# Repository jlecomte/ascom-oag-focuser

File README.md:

# ASCOM-Compatible OAG Focuser

I do not charge anything to create and maintain these open-source projects. But if you would like to say "thanks" for this project, feel free to send any amount through Paypal using the button below. I appreciate your support!

<!-- toc -->

- [Introduction](#introduction)
  * [Is This For You?](#is-this-for-you)
  * [Use As A Standalone Focuser](#use-as-a-standalone-focuser)
- [Finished Product](#finished-product)
- [Demo](#demo)
- [Pre-Requisites](#pre-requisites)
- [Hardware / BOM](#hardware--bom)
- [ASCOM Driver](#ascom-driver)
  * [Downloading And Installing The Driver](#downloading-and-installing-the-driver)
  * [Compiling The Driver (For Developers Only)](#compiling-the-driver-for-developers-only)
  * [Screenshots](#screenshots)
- [Standalone Focuser Application](#standalone-focuser-application)
- [Arduino Firmware](#arduino-firmware)
  * [Microcontroller Compatibility](#microcontroller-compatibility)
  * [Compiling And Uploading The Firmware](#compiling-and-uploading-the-firmware)
- [Electronic Circuit](#electronic-circuit)
- [Mechanical Components](#mechanical-components)
  * [OAG Compatibility](#oag-compatibility)
  * [Gear And Pinion](#gear-and-pinion)
- [Calibration Procedure](#calibration-procedure)
- [Troubleshooting](#troubleshooting)
- [Frequently Asked Questions (FAQ)](#frequently-asked-questions-faq)
- [Credits](#credits)

<!-- tocstop -->

## Introduction

Shortly after I got started in astrophotography, I noticed that the stars in my images were slightly elongated due to some differential flexure somewhere in my imaging system (see [Cloudy Nights thread](https://www.cloudynights.com/topic/775260-good-guiding-but-elongated-stars-along-e-w-direction/) — I strongly suspect that it is sag in my focuser...) The permanent solution was to switch from using a guide scope to using an off-axis guider (OAG) and that immediately resolved my issue. Now, my stars are perfectly round, which is great! For reference, I purchased the [ZWO OAG](https://astronomy-imaging-camera.com/product/zwo-oag) and the accompanying [ZWO 1.25" helical focuser](https://astronomy-imaging-camera.com/product/zwo-1-25%E2%80%B3-helical-focuser).

As good as this sounds, the OAG brought a number of new challenges which I did not have to deal with before. First, when using an OAG, the field of view is very small, which sometimes makes it difficult for the guiding software to detect guide stars. Second, the OAG requires some amount of refocusing when switching filters. Indeed, filters are not always parfocal. Most importantly, a refractor (even an apochromatic triplet...) will focus various wavelengths at different distances, and this is the primary reason why it is required to change the focus of the main imaging camera (using filter offsets) when changing filters. Unfortunately, while the imaging sensor is located _behind_ the filter wheel, the OAG is always placed _before_ the filter wheel (Otherwise, especially when using narrowband filters, you would not be able to find a single guide star... Also, placing the filter wheel further away from the imaging sensor would cause vignetting...) and this is why, under specific conditions (see "Is this For You" paragraph below), the guide camera might show out-of-focus images while the imaging camera is in focus, and even though the guide camera was independently focused while another filter was selected in the filter wheel.

While guiding software like PHD2 can accommodate slightly out-of-focus guide stars by computing their centroid, out-of-focus guide images can contain a drastically lower number of detected guide stars, and those that are detected will have a much lower Signal to Noise Ratio (SNR), further reducing the accuracy of the centroid computation. In some situations, PHD2 may not even be able to detect a single guide star, and guiding will be impossible. This has happened to me in the past, and I was forced to _manually_ refocus the guide camera (independently of the main imaging camera of course, using the OAG helical focuser)

Manually refocusing the guide camera throughout the night is not exactly one of the most enjoyable parts of the hobby, so I looked for ways to automate that. Pegasus Astro sells a motorized OAG named [SCOPS OAG](https://pegasusastro.com/products/scops-oag/). However, it is a little expensive for me ($750 US — although it is a really great looking unit!) Furthermore, I discussed with the [N.I.N.A.](https://nighttime-imaging.eu/) developers on their [Discord server](https://discord.gg/fwpmHU4). Since N.I.N.A. can only connect to a single focuser at a time, there is no good solution yet to deal with SCOPS OAG. It is certainly possible to run a second instance of N.I.N.A. that connects to both SCOPS OAG and the guide camera, but there is no way to have those two N.I.N.A. instances communicate to do something upon filter change.

All of this has led me to design and build my own solution to this problem. In this repository, you will find everything you need to motorize and automatically control the ZWO OAG (list of parts, 3D model, electronic schematics, Arduino firmware, ASCOM driver, standalone ASCOM client application, instructions, etc.) I hope you consider building this project if you find yourself in a similar situation. Please note that the ASCOM driver can be used with SCOPS OAG, there is nothing in the Filter Wheel Proxy implementation that is specific to my device.

### Is This For You?

Not necessarily! It really depends on a lot of factors. For example, if you are using a mirrored telescope, i.e. not a refractor, and if all of your filters come from the same set, e.g., Antlia LRGB filter set, and the filter manufacturer claims they are parfocal, then you may not need this at all because the difference in focus between filters will be so minuscule, you probably won't need to worry about it. However, if you are using a refractor (even an APO triplet), or if you use filters that are not parfocal, you _may_ need this. The only way to find out is to focus your main imaging camera, and then, assuming that you've already defined your filter offsets, go through every single filter in your filter wheel. After every filter change, your imaging application will adjust the focus of your imaging train slightly depending on the filter offset you have defined for the selected filter, and you should look at the image coming out of your guide camera in PHD2. In my case, the stars in my guide camera can be pinpoint when I am using my Luminance filter, but they are large disks when I am on some other filter. That is how you know that this device can be useful for you. This definitely is not for everybody, but the people who have the problem I just described did not really have a good solution until now.

### Use As A Standalone Focuser

Please note that you can use this device, and the accompanying software, to motorize any helical focuser, regardless of how you use that focuser. For example, you could use it to control the focus of a guide scope or even an entire imaging train! Some people have used this project to motorize the focus of a spectrograph. Just remember that if you have a helical focuser that is not from ZWO, you may need to make a few adjustments to the 3D model...

## Finished Product

Here is what the finished product looks like:

And here it is, attached to the ZWO OAG, and fitted with a guide camera:

## Demo

Here is a demo of the system when attached to my telescope, and used as an OAG focuser:

The following video shows what the guide camera sees with and without the OAG focuser upon switching to a different filter:

## Pre-Requisites

* A Windows computer (Windows 10 or newer)
* [Microsoft Visual Studio](https://visualstudio.microsoft.com/) (FYI, I used the 2022 edition...)
* [ASCOM Platform](https://ascom-standards.org/)
* [ASCOM Platform Developer Components](https://ascom-standards.org/COMDeveloper/Index.htm)
* [Arduino IDE](https://www.arduino.cc/en/software)
* [FreeCAD](https://www.freecadweb.org/), a free and open-source 3D parametric modeler
* A 3D printer able to print PETG, and a slicer (I use a heavily upgraded Creality Ender 3 v2, and Ultimaker Cura)
* A few basic tools that any tinkerer must own, such as a breadboard, a soldering iron, etc.

## Hardware / BOM

* [ZWO 1.25" helical focuser](https://bit.ly/47JOTRL) or equivalent.
* Arduino-compatible microcontroller board with built-in EEPROM support. I used an [Arduino Nano clone with a USB-C connector (~$10 USD on Amazon for a pack of 3...)](https://www.amazon.com/dp/B09DKHWSY9?tag=darkskygeek-20)
* [ULN2003 Darlington transistor array](https://www.amazon.com/dp/B0CBM23ZJ3?tag=darkskygeek-20) to control the stepper motor using the Arduino's digital I/O pins.
* [28BYJ-48 stepper motor (5V)](https://www.amazon.com/dp/B01CP18J4A?tag=darkskygeek-20)
* [LEDs](https://www.amazon.com/dp/B09XDMJ6KY?tag=darkskygeek-20) and [resistors](https://www.amazon.com/dp/B08FD1XVL6?tag=darkskygeek-20) — These are not required, but they can be useful to debug the firmware while prototyping.
* Connectors — I used [JST-XH connectors](https://www.amazon.com/dp/B01MCZE2HM?tag=darkskygeek-20), only because I already had a bunch of them, along with [a crimping tool](https://www.amazon.com/dp/B078WNZ9FW?tag=darkskygeek-20).
* [Capacitors](https://www.amazon.com/dp/B07PBQXQNQ?tag=darkskygeek-20) — Any 10 to 20µF cpacitor should work (this is just a bulk capacitor, so the exact value does not matter)
* [M2 Threaded Inserts](https://www.amazon.com/dp/B0B8GN63S2?tag=darkskygeek-20)
* [M3 Threaded Inserts](https://www.amazon.com/dp/B0BQJ6CRNJ?tag=darkskygeek-20)

## ASCOM Driver

### Downloading And Installing The Driver

Starting with version `1.0.5`, you can install the ASCOM driver, as well as the standalone focuser control application, by running the executable setup file that you will find in the [releases page](https://github.com/jlecomte/ascom-oag-focuser/releases). By default, it places files under `C:\Program Files (x86)\Dark Sky Geek\OAG Focuser ASCOM Driver`.

### Compiling The Driver (For Developers Only)

Open Microsoft Visual Studio as an administrator (right-click on the Microsoft Visual Studio shortcut, and select "Run as administrator"). This is required because when building the code, by default, Microsoft Visual Studio will register the compiled COM components, and this operation requires special privileges (Note: This is something you can disable in the project settings...) Then, open the solution (`ASCOM_Driver\ASCOM.DarkSkyGeek.OAGFocuser.sln`), change the solution configuration to `Release` (in the toolbar), open the `Build` menu, and click on `Build Solution`. As long as you have properly installed all the required dependencies, the build should succeed and the ASCOM driver will be registered on your system. The binary file generated will be `ASCOM_Driver\bin\Release\ASCOM.DarkSkyGeek.OAGFocuser.dll`. You may also download this file from the [Releases page](https://github.com/jlecomte/ascom-oag-focuser/releases).

### Screenshots

The ASCOM driver registers two new components: `ASCOM.DarkSkyGeek.FilterWheelProxy`, which implements the `IFilterWheelV2` ASCOM interface, and `ASCOM.DarkSkyGeek.OAGFocuser`, which implements the `IFocuserV3` ASCOM interface. Both components have their own settings dialog. Here is what the filter wheel settings dialog looks like:

And here is what the focuser settings dialog looks like:

## Standalone Focuser Application

Open the `Focuser_App\ASCOM.DarkSkyGeek.FocuserApp.sln` solution in Microsoft Visual Studio, change the solution configuration to `Release` (in the toolbar), open the `Build` menu, and click on `Build Solution`. Very simple! The binary file generated will be `Focuser_App\bin\Release\ASCOM.DarkSkyGeek.FocuserApp.exe`. You may also download this file from the [Releases page](https://github.com/jlecomte/ascom-oag-focuser/releases). Here is what that little standalone application looks like:

This application allows you to connect to and control DarkSkyGeek’s OAG focuser, and in particular, it enables you to test various backlash compensation values as well as set the zero position. If you use a SCOPS OAG, I can only assume that it came with its own standalone application with similar functionality...

## Arduino Firmware

### Microcontroller Compatibility

All Arduino-compatible microcontrollers that have a **built-in EEPROM** should work. Unfortunately, this excludes the popular [Seeeduino XIAO](https://www.seeedstudio.com/Seeeduino-XIAO-Arduino-Microcontroller-SAMD21-Cortex-M0+-p-4426.html) (one of my favorite microcontroller boards for hobby projects...) If you insist on using a unit that does not have a built-in EEPROM, you will have to customize the firmware to fit your needs. You could technically use a separate EEPROM chip, or you could use the [`FlashStorage` library](https://github.com/cmaglie/FlashStorage) or the [`FlashStorage_SAMD` library](https://github.com/khoih-prog/FlashStorage_SAMD), or you could simply disable the EEPROM code (in which case the device will not remember its last position after a power cycle...) There are quite a few options to choose from, but I recommend using something like an Arduino Nano for example, which is small, affordable, and has everything you need.

**Note:** I tried several Arduino nano clones, and they do not all work. Some of them seem to work, but not reliably. I did not investigate too deeply, but I think it is because their BOD (Brown Out Detection) levels are set too low. When the motor turns, the voltage used to power the microcontroller will drop slightly, and if it drop below a certain level, some units will simply reset themselves in an act of self-protection. So, I strongly recommend the unit linked above, in the BOM list.

### Compiling And Uploading The Firmware

* If needed, add support for the board that you are using in your project.
* You may want to customize the name of the device when connected to your computer. To do that, you will have to update the appropriate `usb_product` key in the appropriate `boards.txt` file... I cannot give you specific instructions for that because they depend on the exact board you are using.
* Finally, connect your board to your computer using a USB cable, open the sketch file located at `Arduino_Firmware\Arduino_Firmware.ino`, and click on the `Upload` button in the toolbar.

## Electronic Circuit

The electronics circuit is fairly straightforward. I included a Fritzing file in the `Electronics/` folder. Here are the schematics:

Here is what the prototype circuit looks like:

Here is what the PCB looks like when rendered in KiCad:

Here is what the real PCB looks like:

## Mechanical Components

### OAG Compatibility

In case you are planning to use this electronic focuser with an OAG, please note that [the standard version](3D_Files/Standard-Version/) is compatible (out of the box) with the following OAGs:

* ✅ **ZWO OAG** (standard version)
* ✅ **ZWO OAG-L** (large version) via [this adapter](3D_Files/ZWO-OAG-L/Adapter.FCStd).
* ✅ **Askar OAG**
* ✅ **Player One OAG** (MIN or MAX)

Additionally, an OpenSCAD model designed for the **Celestron OAG** was generously provided by [Endymion42](https://github.com/Endymion42). For more information and photographs, please refer to [this GitHub issue](https://github.com/jlecomte/ascom-oag-focuser/issues/10). The files can be found [here](3D_Files/Celestron-OAG/). **Important note: I will not provide any support whatsoever for this version, so use at your own risk!**

And finally, please note that this electronic focuser is NOT compatible with the following OAGs (at least not without a significant design change):

* 🛑 **QHY OAG**
* 🛑 **Touptek OAG**
* 🛑 **OGMA OAG** — The helical focuser cannot be removed, so you would have to slightly tweak the design of this project to make it fit.
* 🛑 **Antlia OAG** — The helical focuser can be detached from that unit, exposing an M42 male thread, so you would think it might work. However, due to the square OAG body, the stepper motor gets in the way. In my design, the stepper motor sticks out under the body of the electronic focuser to minimize the space the entire unit takes when used with a round OAG. **Note:** Some people have successfully adapted my design to flip the motor around and make it work with this unit.

### Gear And Pinion

In [the first version of this project](https://github.com/jlecomte/ascom-oag-focuser/tree/v1), I was using helical gears. However, this was not a very smart choice because the axial force that results from this design, and the fact that the stepper motor shaft has a bit of longitudinal play caused the backlash to be a bit higher than I would have liked. While it still worked well (thanks to backlash compensation), this new version uses a herringbone pattern for the gear and pinion:

It turns out that gears are easy to make on a 3D printer, and work flawlessly. However, here are a few tips I found useful:

* Dry your filament to reduce problems, specifically stringing to a minimum
* Use the proper Z offset, and (if needed) set the initial layer horizontal expansion value in Cura to a negative number, e.g., -0.2mm. It is critical to prevent the dreaded "elephant's foot" (squishing of the first layer)
* To ensure that the first layer adheres well, clean your build plate (I use denatured alcohol)

Another trick that also helped get great results was to slightly loosen the focuser (there are 4 tiny set screws on the ZWO focuser that you can loosen _ever so slightly_ to make it easier to rotate the knurled knob) because these small stepper motors don't have that much torque...

The focuser gear slips onto the knurled knob of the helical focuser. The pinion slips onto the motor shaft, although it might require a light hammer blow to get it fully seated. It is not necessary to use any glue to keep the gears in place.

## Calibration Procedure

Before you can use this device, you have to calibrate it. Here is the procedure:

1. **Filter Offsets Measurement**

   Measuring filter offsets is something you have probably already done because it allows you to run an autofocus routine using your luminance (L) filter, which can be done with very short exposures, thereby saving a lot of time (it is also more accurate). Enter the filter offsets in your imaging application, e.g., N.I.N.A., as well as in the settings dialog of the `DarkSkyGeek’s Filter Wheel Proxy For OAG Focuser` ASCOM device (see screenshot above). Remember that it is critical that your imaging application and the driver have the same filter offset values!

   **Note:** If you measure your filter offsets with a reducer, they will be different. Don't worry about that. Do the entire calibration procedure with your standard astrophotography setup. Once properly set up, the OAG focuser configuration will not need to change whether or not you add a reducer to your imaging train.

2. **Backlash Measurement**

   There are many sources of backlash in this system. The stepper motor itself, due to its internal gearbox, already has some amount of backlash. The 3D printed gear and pinion also have some backlash. And finally, the helical focuser has some backlash as well. All of those sources combine. Thankfully, compensating for backlash is easy and supported by the software in this repository. The trick is to first measure the amount of backlash in your system. That is done using a dial gauge. Please refer to the video below for more details.

   Using the standalone focuser control application, setting a backlash compensation of 0, move in one direction by a large amount. Then, repetitively move in small increments in the opposite direction until the dial indicator starts moving. In my setup, I have a total of about 60 steps of backlash, so I set the backlash compensation amount to 150 (the software uses the so-called "overshoot" backlash compensation method) and it works absolutely flawlessly! Enter the value of the backlash, in number of steps (150 in my case), in the settings dialog of the `DarkSkyGeek’s Filter Wheel Proxy For OAG Focuser` ASCOM device (see screenshot above)

3. **Zero Position**

   Manually rotate the OAG focuser until it hits its mechanical zero position. Connect the OAG focuser to a computer (assuming you had previously installed the OAG focuser ASCOM driver on that computer), open the standalone focuser app, connect to the device, and click on the "Set Zero position!" button.

4. **Steps Ratio Measurement**

   The "steps ratio" allows the Filter Wheel Proxy ASCOM driver to answer the following question: Upon filter change, the main focuser has to move n steps in this direction. How many steps does the OAG focuser need to move, and in which direction?

   The best way to measure the steps ratio is to use 2 instances of N.I.N.A. The first instance is connected to the telescope focuser and the main imaging camera. The second instance is connected to the OAG focuser and the guide camera. Then, follow these steps:

   * Run an autofocus routine in both N.I.N.A. instances (start with the one that controls the telescope focuser and the main imaging camera)
   * Take note of the position of the OAG focuser.
   * Move the telescope focuser by, for example, 300 steps outward.
   * Run another autofocus routine on the second N.I.N.A. instance (the one that controls the OAG focuser and the guide camera)
   * Subtract the new position of the OAG focuser with the initial position, and divide that number by the number of steps you moved the main telescope focuser (300 in our example). That will give you the steps ratio. Note that this will be a negative number. In my case, the steps ratio is -2.64.
   * You can run the autofocus routine several times, and average the positions obtained to increase accuracy.
   * Enter the steps ratio in the settings dialog of the `DarkSkyGeek’s Filter Wheel Proxy For OAG Focuser` ASCOM device (see screenshot above)

5. **Test**

   Once you have calibrated the OAG Focuser, you can close the second instance of N.I.N.A. and open PHD2. Use the first instance of N.I.N.A. as you normally would, although instead of connecting your filter wheel directly, you will connect to the `DarkSkyGeek’s Filter Wheel Proxy For OAG Focuser` device. Looking at the PHD2 live view, change the filter in the filter wheel and watch the PHD2 live view becoming blurry and then sharp again, automatically! Isn't technology beautiful?!

This procedure is explained in great detail in the following video:

## Troubleshooting

**The standalone focuser application is not able to connect to the device**

**Step 1:** On Windows, open the Device Manager, and expand the `Ports (COM & LPT)` section. Connect the Arduino. You should see a new COM port appear. If you don't, there is a problem with Windows, the Arduino, or the USB cable.

**Step 2:** Assuming that a new COM port appeared in step 1, open the driver settings dialog from the standalone focuser application, and ensure that you have the `Auto-Detect COM port` option enabled.

**Step 3:** Make sure that no other application is currently using the COM port assigned to the device. On Windows, a single process can be connected to a COM port at any given time, so if you happen to be running the Arduino IDE (for example) at the same time, it will have likely automatically connected to the Arduino via the COM port, and the standalone focuser application will not be able to connect.

**Step 4:** If all else fails, look for the driver logs under `<DOCUMENTS FOLDER>\ASCOM\Logs <DATE>\` and open the most recent file. Feel free to open an issue, and paste the content of the log file.

**The focuser turns in the wrong direction**

Depending on how you wire the stepper motor, it may turn in different directions. This is especially important when you first try the device, because its position is set to 0 by default and the driver will throw an error if the position becomes negative. So if you encounter an error on first try, don't worry! Disconnect the focuser in the application (no need to disconnect the USB cable...), open the focuser settings dialog, toggle the "Reverse Rotation" option (see screenshot above), and click OK. Then, connect to the focuser and try again.

## Frequently Asked Questions (FAQ)

**I built this project and it does not work, can you help?**

_Maybe. As indicated in the `LICENSE` file, I do not provide any official guarantee or support. That being said, if you open a GitHub issue in this repository and ask nicely, I will likely respond. Just make sure that you provide all the necessary details so that I understand what the issue might be. While on that note, keep in mind that troubleshooting an issue on your own is by far the best way to learn new things._

**Why did you not use the `Stepper` or `AccelStepper` library in the Arduino firmware?**

_It might seem strange that I decided to "manually" control the stepper motor instead of using the standard [`Stepper` library](https://www.arduino.cc/reference/en/libraries/stepper/) or the popular [`AccelStepper` library](https://www.arduino.cc/reference/en/libraries/accelstepper/). There are two reasons for that:_

1. _I need to be able to handle incoming requests while the motor is moving, e.g., `COMMAND:FOCUSER:ISMOVING` or `COMMAND:FOCUSER:HALT`. This is not possible with any of the aforementioned libraries._
2. _To save power, to prevent heat buildup, and to eliminate vibrations, I de-energize the stepper motor by setting all the pins to LOW once it has reached the desired position. This is also not supported by any of the aforementioned libraries, and it makes a huge difference! If you don't believe me, try commenting out that part of the code, and play with the firmware for a little while (you don't even need to actively move the motor). Then, feel how hot the motor gets... Also, feel how much the motor vibrates while energized, and consider the impact that might have on your images..._

**Why is backlash compensation not implemented in the focuser driver?**

_The software included in this repository (specifically the `FilterWheelProxy` ASCOM component) was designed and implemented so that it may be used with other OAG focusers, including commercial units such as the SCOPS OAG, and I have no idea whether their driver handles backlash compensation. This way, no matter which focuser you use to adjust the focus of your guide camera, as long as its driver implements the standard `IFocuserV3` ASCOM interface, this will work and you will enjoy the benefits of backlash compensation!_

**What is the positional accuracy of this focuser?**

_Using a precision dial indicator (see "Backlash Measurement" section), I was able to measure the positional accuracy of this device (move 1,000 steps in one direction, move 1,000 steps in the opposite direction, and measure the difference between the starting and ending positions). Astoundingly, it is of the order of about 10μm!_

**My antivirus identifies your setup executable file as a malware (some kind of Trojan)**

_This is a false detection, extremely common with installers created with [Inno Setup](https://jrsoftware.org/isinfo.php) because virus and malware authors also use Inno Setup to distribute their malicious payload... Anyway, there isn't much I can do about this, short of signing the executable. Unfortunately, that would require a code signing certificate, which costs money. So, even though the executable I uploaded to GitHub is perfectly safe, use at your own risk!_

## Credits

I would like to thank _Christophe de la Chapelle_ of the popular French-language YouTube channel [La Chaîne Astro](https://www.youtube.com/c/cdlc48) because he gave me the idea to build a focuser for my OAG after he demonstrated how he had built a simple focuser using 3D printed parts and a stepper motor for his telescope.

I would like to also thank _Stefan Berg_, creator of [N.I.N.A.](https://nighttime-imaging.eu/), and _Linwood Ferguson_ (see [his web site](https://www.captivephotons.com/Photography/Astrophotography/)) for giving me the idea to create a "proxy" filter wheel component while discussing the design of this system on the [N.I.N.A. Discord server](https://discord.gg/fwpmHU4).

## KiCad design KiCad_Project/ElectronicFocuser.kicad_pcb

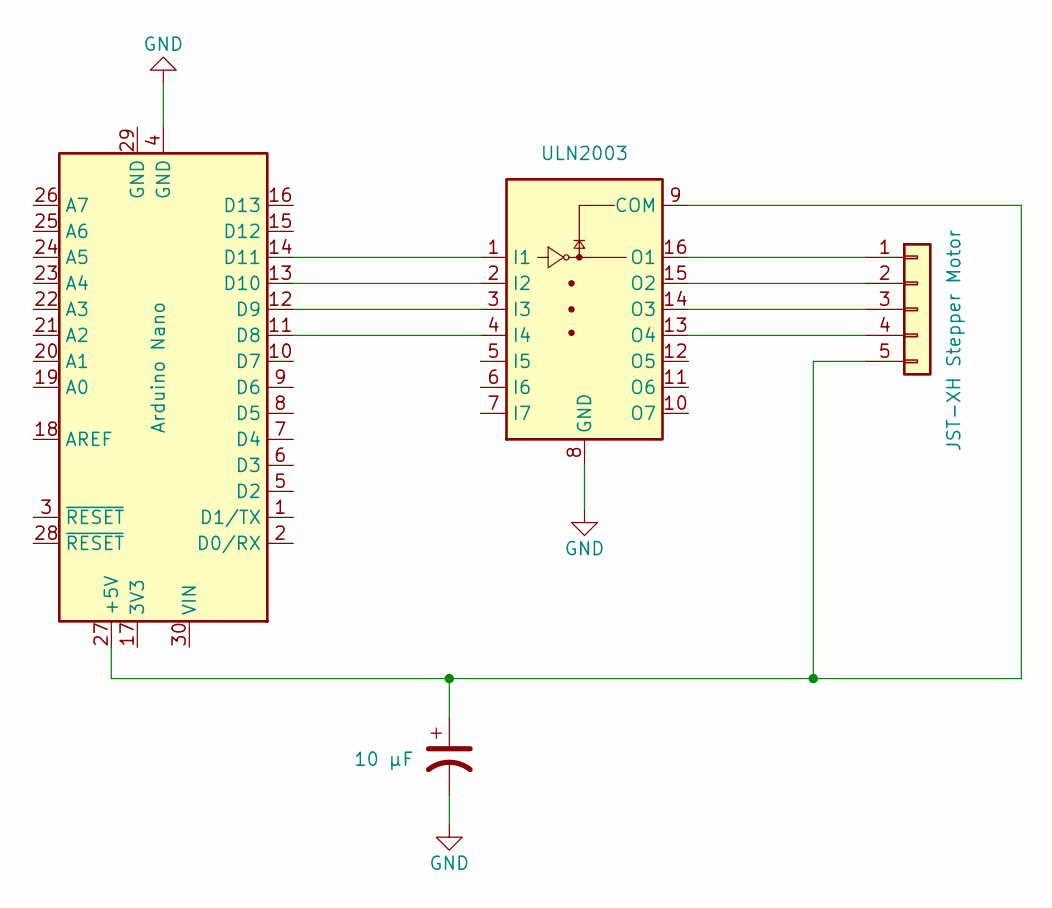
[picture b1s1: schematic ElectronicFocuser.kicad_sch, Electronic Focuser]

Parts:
A1: Arduino Nano; Arduino_Nano
C1: 10 µF; CP_Radial_D4.0mm_P2.00mm
J1: JST-XH Stepper Motor; JST_XH_B5B-XH-A_1x05_P2.50mm_Vertical
U1: ULN2003; DIP-16_W7.62mm

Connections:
GND: A1.4 (GND), C1.2, U1.8 (GND)
unnamed: A1.11 (D8), U1.4 (I4)
unnamed: A1.12 (D9), U1.3 (I3)
unnamed: A1.13 (D10), U1.2 (I2)
unnamed: A1.14 (D11), U1.1 (I1)
unnamed: A1.27 (+5V), C1.1, J1.5, U1.9 (COM)
unnamed: J1.1, U1.16 (O1)
unnamed: J1.2, U1.15 (O2)
unnamed: J1.3, U1.14 (O3)
unnamed: J1.4, U1.13 (O4)

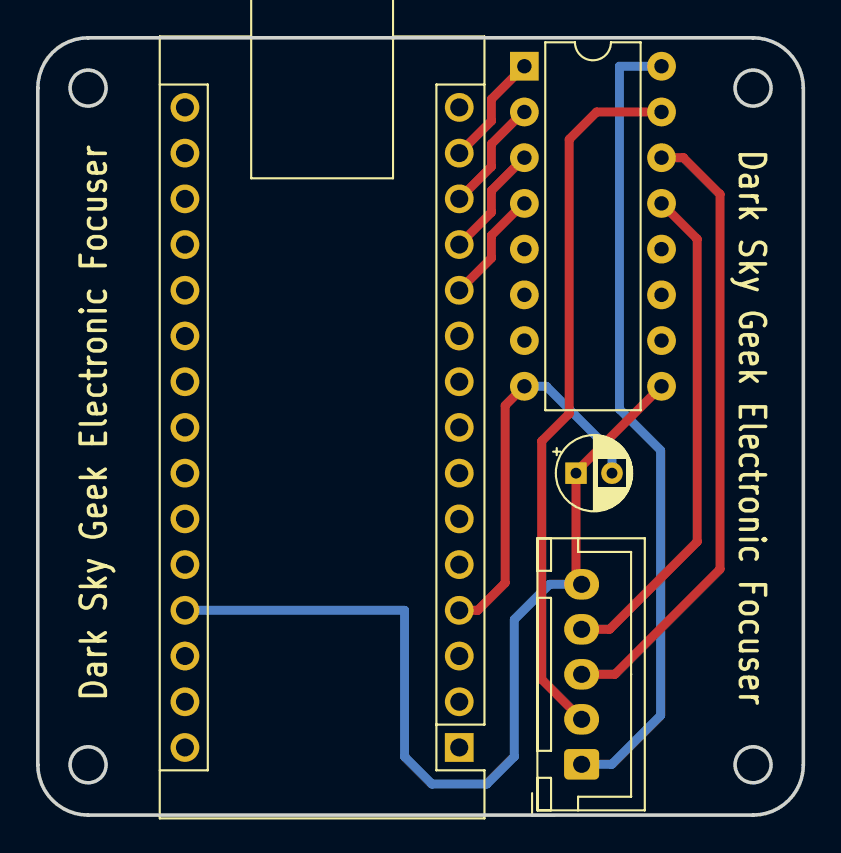
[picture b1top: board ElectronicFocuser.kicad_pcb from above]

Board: 2 copper layers, 42.5 x 43.2 mm, 4 parts (0 on the bottom side), 10 nets.

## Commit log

2022-05-22 Updated project file
2022-05-22 Fixed initial set of bugs
2022-05-23 First working working!
2022-05-23 Fix heat build up by powering off the stepper when idle
2022-05-23 Updated comment
2022-05-23 Code cleanup + added backlash handling and leveraged step ratio
2022-05-24 Added first 3D files
2022-05-24 Added images
2022-05-25 Added standalone focuser app
2022-05-25 Fixed lots and lots of small - and not so small - issues
2022-05-25 Small tweaks to make the driver work with scops OAG
2022-05-25 Few minor fixes to focuser app
2022-05-25 Added electronics schematics
2022-05-25 Updated images
2022-05-25 Renamed standalone focuser app binary
2022-05-25 Updated README and images
2022-05-25 Added copyright header that was missing in a few files
2022-05-26 Fixed small routing issue in electronics schematics
2022-05-28 Allow focuser to reverse rotation due to gearing
2022-06-06 Added all necessary 3D files
2022-06-16 Added calibration procedure
2022-06-25 Fixed minor bugs found during testing
2022-07-18 Fixed bug reported by a member of the CloudyNights forum
2022-09-28 Catch ANY exception during initialization to ensure we can deal with junk stored in the ASCOM profile...
2022-09-28 Removed conversions in static initializer to avoid the possibility to any exception
2023-06-05 Write the correct value for autoDetectComPort
2023-12-02 Decreased connection time
2023-12-02 Inno Setup installer
2023-12-02 Updated install script
2023-12-04 Do not register for COM interop
2023-12-15 Updated assets for v2
2023-12-19 v2 WIP
2023-12-31 Updated PCB layout to make room for attachments
2023-12-31 Reshaped gears
2024-01-05 Updated 3D model and printed gears images
2024-01-06 Updated 3D model
2024-01-13 Updated 3D files
2024-01-21 Minor updates for v2
2024-02-06 Added note about OAG compatibility
2024-02-11 Updated models to cover several different OAG models
2024-02-12 Updated 3D model for ZWO OAG-L
2024-02-12 Updated 3D models for standard versions 1 and 2
2024-02-18 Updater adapter for ZWO OAG-L
2024-02-18 Updated 3D models
2024-02-19 Fixed ZWO OAG-L adapter
2024-02-20 Updated model for standard version 2
2024-02-20 Single standard version
2024-02-23 Addressed issue #11
2024-02-23 OAG Compatibility + Fixes (#12)
2024-02-24 Fixed a few UI issues with the standalone focuser app
2024-02-27 Added Celestron OAG model files contributed by Endymion42 - see issue #10
2024-03-09 Update MainForm.cs
    Current version throws exception updating from non uni thread when clicking on the left and right arrows
2024-03-09 Update MainForm.cs (#13)
    Current version throws exception updating from non uni thread when clicking on the left and right arrows
2024-03-09 Fix syntax error and bumped minor version number on standalone focuser app
2024-03-10 Replaced char that is not properly displayed by the installer
2024-03-11 Fixed 3D model for standard version
2024-03-12 Small tweak to the 3D models
2024-03-16 Small tweak to the 3D model for better gear meshing
2024-03-16 Tweak the gear to better fit the ZWO helical focuser
2024-03-19 Forgot to connect pin 9 of ULN2003, which could cause electrical issues due to EMF
2024-03-23 Added support for profiles
2024-03-23 Preparing for version 1.2.0
2024-03-23 Added profile support and set "reverse rotation" to be on by default (#14)
2024-03-23 Updated screenshot
2024-03-26 Code cleanup and persist profile to disk instead of using the ASCOM profile
2024-09-18 Fix exception on writing Last COM Port setting to ASCOM profile
    Writing the "Last COM Port" value to the ASCOM profile of the focuser
    throws an exception, because the device type of the profile has not been
    set to "Focuser", so it is "Telescope" by default.
    This means that if auto-detecting the COM port is off in the focuser
    app, the connection always fails.
    The device type was being set inside an "if" clause in the code, meaning
2024-11-02 Support selecting a new profile via custom action when the device is connected
2025-02-23 eat \r character to enable manually testing the OAG-EAF
2025-02-23 Support Xiao RP2040 Board & other RP2040 boards
2025-03-28 Implemented Half-Step, added missing eeprom.commit for rp2040, pe-define pins for some boards, initialize gpio pins to zero to save power
2025-08-24 Add Alignment Tool STL

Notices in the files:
KiCad_Project/ElectronicFocuser.kicad_sch:
License: MIT
